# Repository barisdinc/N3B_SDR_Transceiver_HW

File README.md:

# N3B
V/U/SHF and QO-100 SDR Transceiver Project

This project is a SDR receiver transceiver project initiated to have a portable QO-100 Satellite ground station which can receiver on 739 MHz (direct output of a standard TV LNB) and transmit on 2.4 GHz QO-100 uplink frequency.
The basic idea of the SDR is based on Arjante Marvelde's implementation of Guido's uSDX implementation on raspberry pi pico (https://github.com/ArjanteMarvelde/uSDR-pico/).

Instead of HF components as Tyloe detector Analog Devices's IQ modulator and demodulator chips are chosen to be the IQ components.

I will update the documentation as soon as possible.
Baris DINC
OH2UDS / TA7W

initial pictures of qocurrent work done
initial pictures of the working HW 

OH2UDS / TA7W.

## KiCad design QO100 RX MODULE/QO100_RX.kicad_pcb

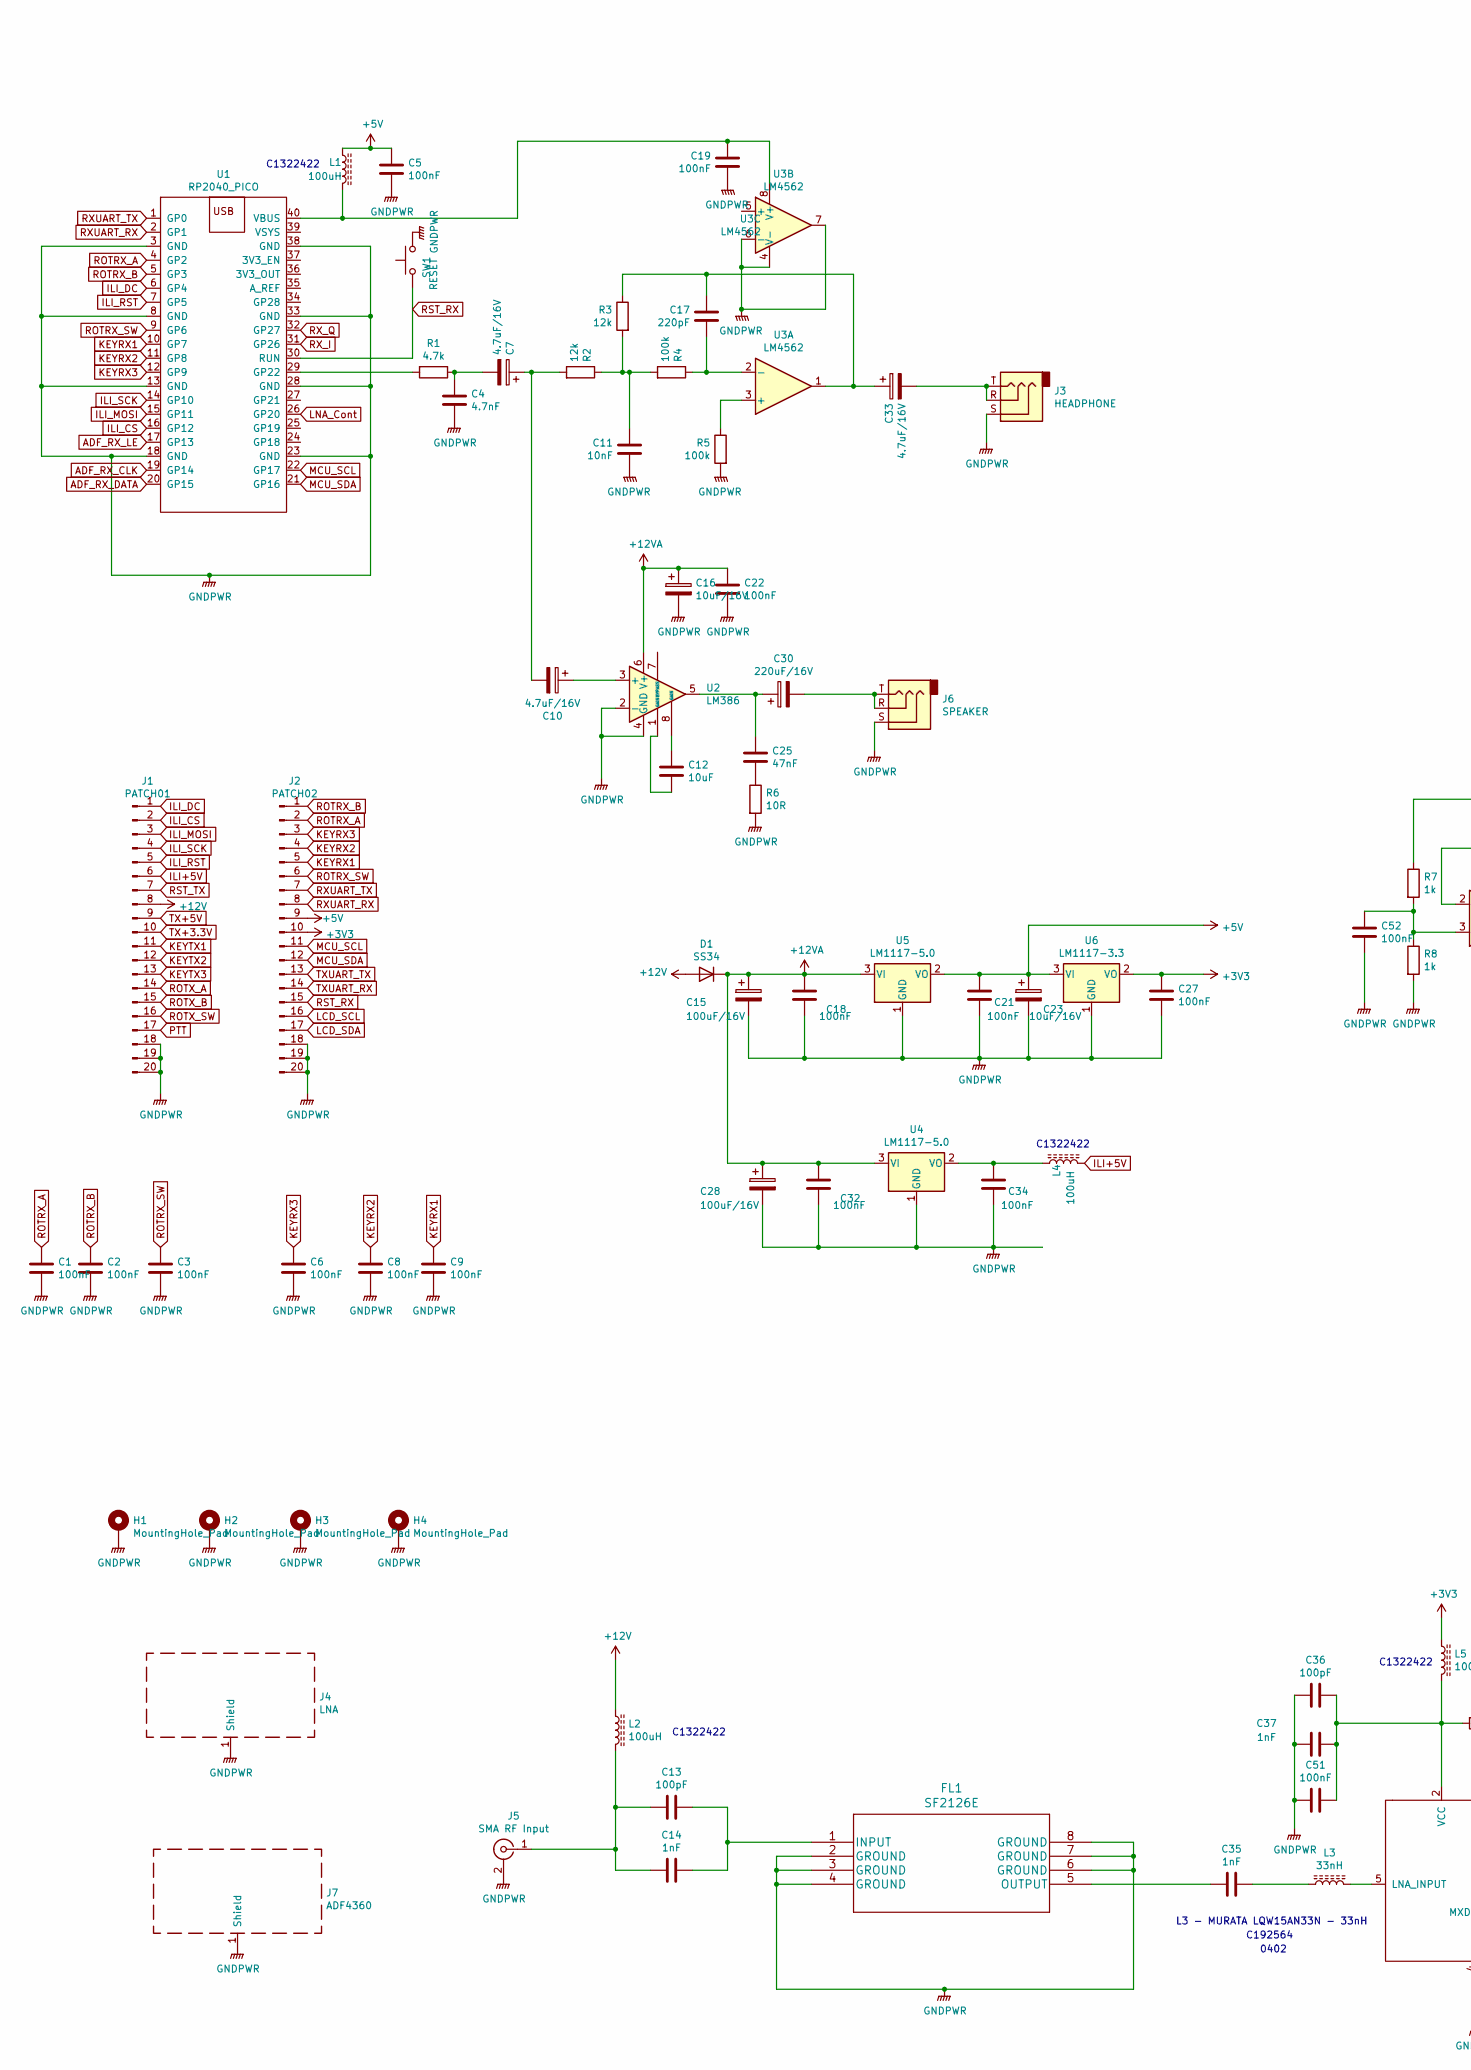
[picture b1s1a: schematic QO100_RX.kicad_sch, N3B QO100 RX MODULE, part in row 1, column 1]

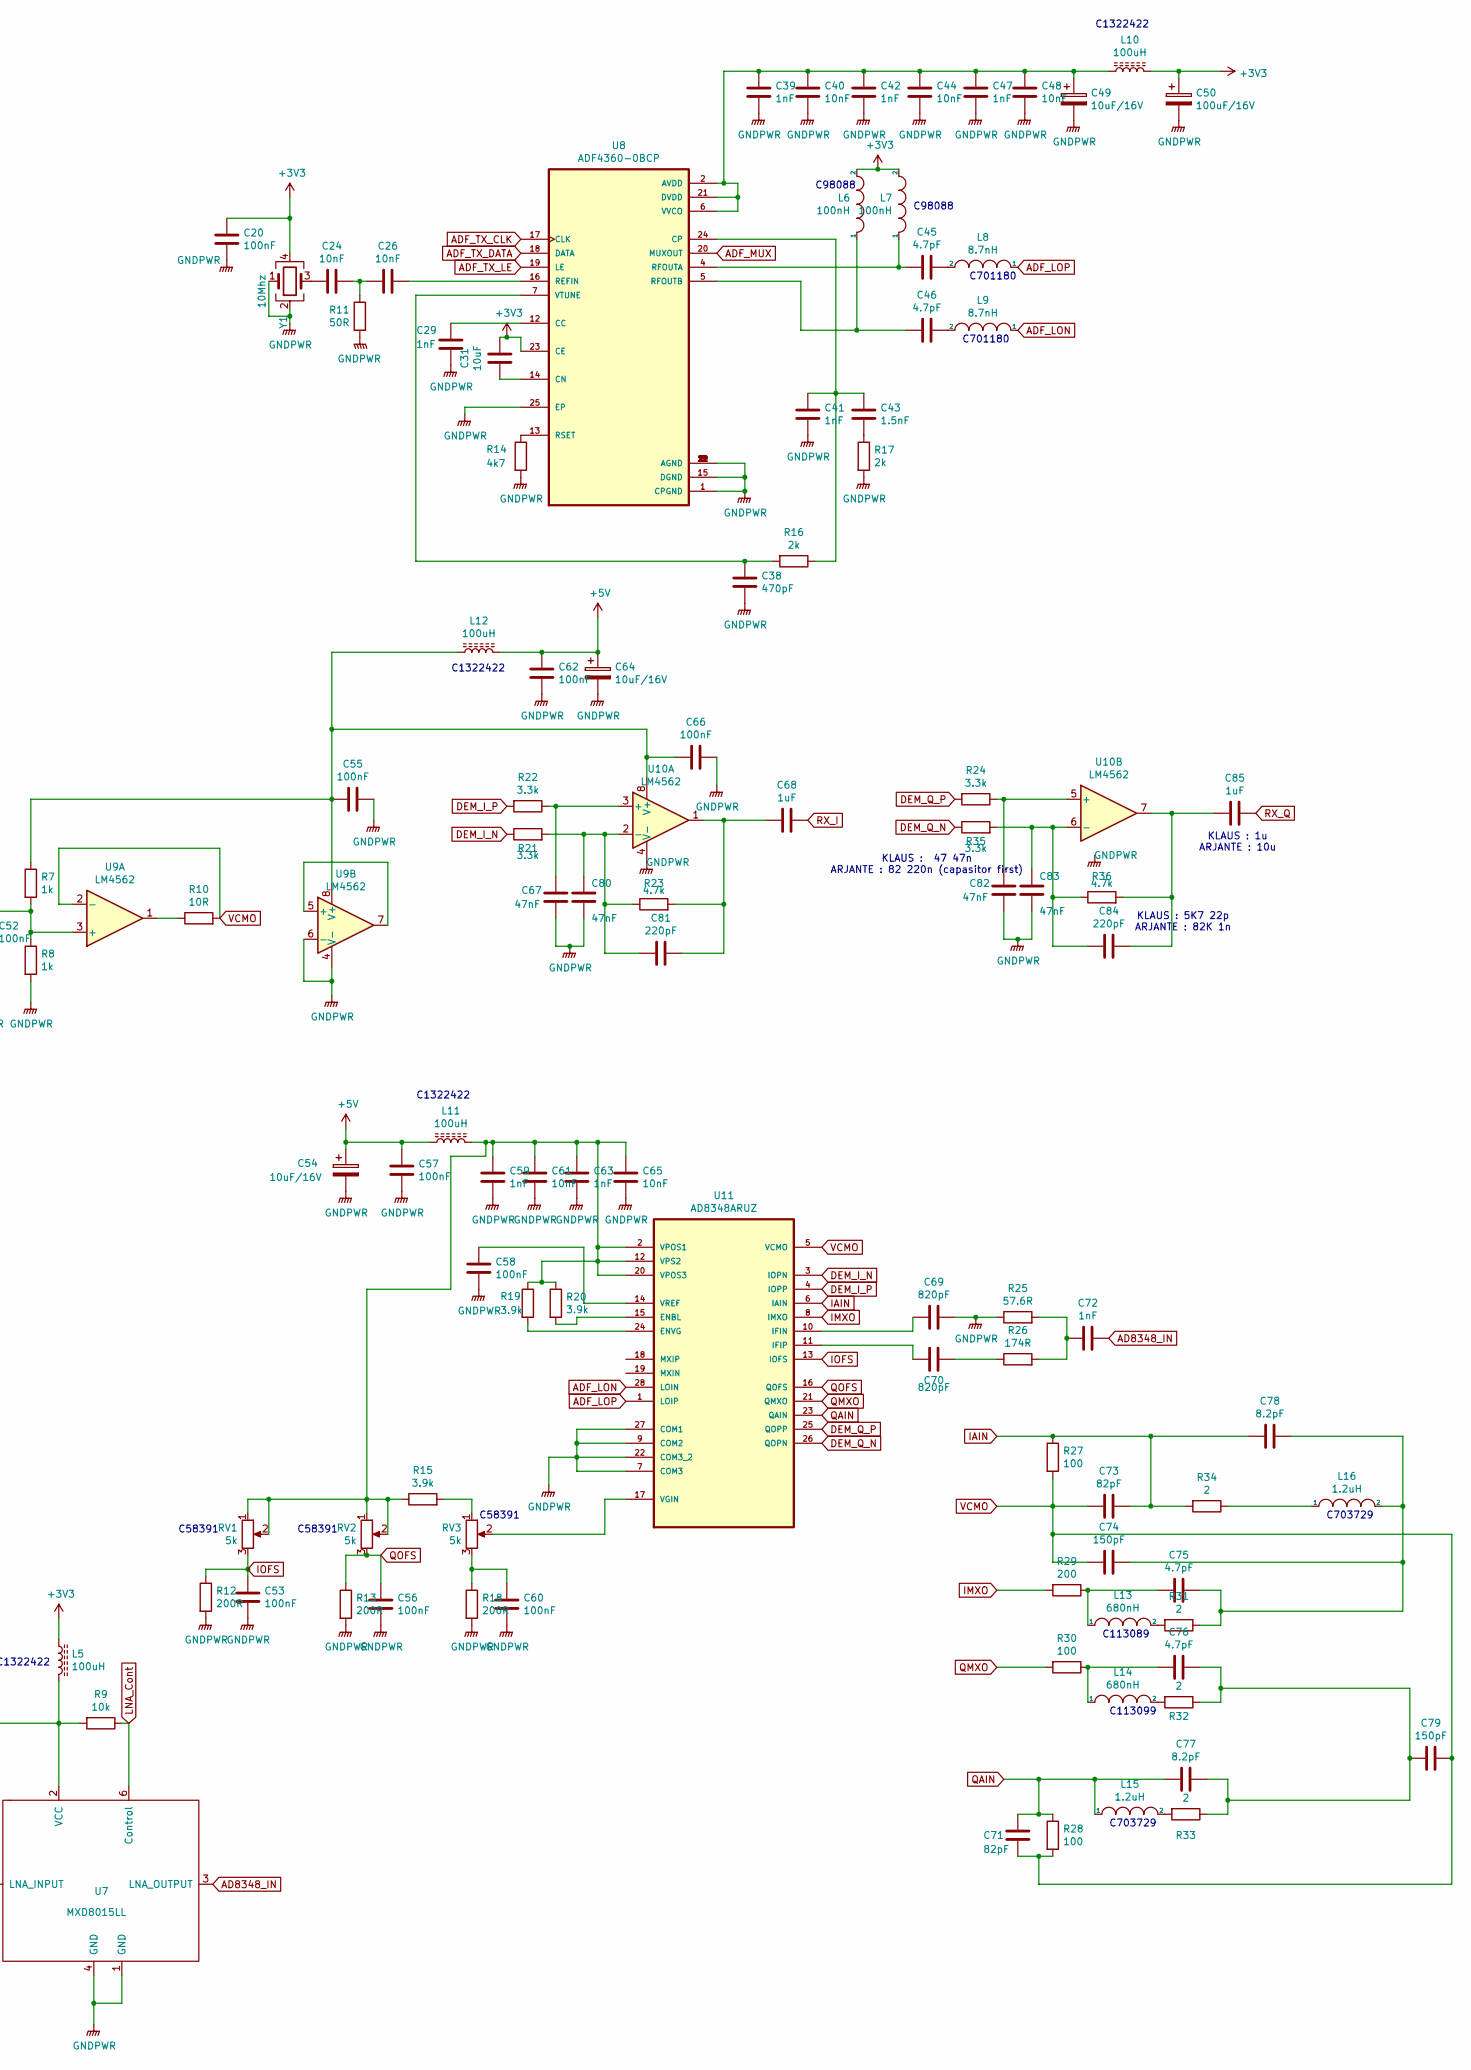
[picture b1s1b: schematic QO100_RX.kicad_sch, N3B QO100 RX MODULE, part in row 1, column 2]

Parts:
C1, C2, C3, C5, C6, C8, C9, C18, C19, C20, C21, C22, C27, C32, C34, C51, C52, C53, C55, C56, C57, C58, C60, C62, C66: 100nF; C_0805_2012Metric
C4: 4.7nF; C_0805_2012Metric
C7, C10, C33: 4.7uF/16V; CP_Elec_4x5.4
C11, C24, C26, C40, C44, C48, C61, C65: 10nF; C_0805_2012Metric
C12, C31: 10uF; C_0805_2012Metric
C13, C36: 100pF; C_0805_2012Metric
C14, C29, C35, C37, C39, C41, C42, C47, C59, C63, C72: 1nF; C_0805_2012Metric
C15, C28, C50: 100uF/16V; CP_Elec_6.3x7.7
C16, C23, C49, C54, C64: 10uF/16V; CP_Elec_4x5.4
C17, C81, C84: 220pF; C_0805_2012Metric
C25, C67, C80, C82, C83: 47nF; C_0805_2012Metric
C30: 220uF/16V; CP_Elec_6.3x7.7
C38: 470pF; C_0805_2012Metric
C43: 1.5nF; C_0805_2012Metric
C45, C46, C75, C76: 4.7pF; C_0805_2012Metric
C68, C85: 1uF; C_0805_2012Metric
C69, C70: 820pF; C_0805_2012Metric
C71, C73: 82pF; C_0805_2012Metric
C74, C79: 150pF; C_0805_2012Metric
C77, C78: 8.2pF; C_0805_2012Metric
D1: SS34; D_SMA
FL1: SF2126E
H1, H2, H3, H4: MountingHole_Pad; MountingHole_3.2mm_M3_DIN965_Pad
J1: PATCH01; PinHeader_1x20_P2.54mm_Vertical
J2: PATCH02; PinHeader_1x20_P2.54mm_Vertical
J3: HEADPHONE; Jack_3.5mm_PJ-320B-SMT_Horizontal_CORR
J4: LNA; Laird_Technologies_BMI-S-102_16.50x16.50mm
J5: SMA RF Input; SMA_Samtec_SMA-J-P-X-ST-EM1_EdgeMount
J6: SPEAKER; Jack_3.5mm_PJ-320B-SMT_Horizontal_CORR
J7: ADF4360; Laird_Technologies_BMI-S-204-F_32.00x32.00mm
L1, L2, L4, L5, L10, L11, L12: 100uH; L_1210_3225Metric
L3: 33nH; L_0402_1005Metric
L6, L7: 100nH; L_0603_1608Metric
L8, L9: 8.7nH; L_0603_1608Metric
L13, L14: 680nH; L_0805_2012Metric
L15, L16: 1.2uH; L_0805_2012Metric
R1, R23, R36: 4.7k; R_0805_2012Metric
R2, R3: 12k; R_0805_2012Metric
R4, R5: 100k; R_0805_2012Metric
R6, R10: 10R; R_0805_2012Metric
R7, R8: 1k; R_0805_2012Metric
R9: 10k; R_0805_2012Metric
R11: 50R; R_0805_2012Metric
R12, R13, R18: 200R; R_0805_2012Metric
R14: 4k7; R_0805_2012Metric
R15, R19, R20: 3.9k; R_0805_2012Metric
R16, R17: 2k; R_0805_2012Metric
R21, R22, R24, R35: 3.3k; R_0805_2012Metric
R25: 57.6R; R_0805_2012Metric
R26: 174R; R_0805_2012Metric
R27, R28, R30: 100; R_0805_2012Metric
R29: 200; R_0805_2012Metric
R31, R32, R33, R34: 2; R_0805_2012Metric
RV1, RV2, RV3: 5k; Potentiometer_Bourns_3314J_Vertical
SW1: RESET; SW_Push_1P1T_NO_6x6mm_H9.5mm
U1: RP2040_PICO; RPI2040_PICO_SMD
U2: LM386; SO-8_3.9x4.9mm_P1.27mm
U3, U9, U10: LM4562; SO-8_3.9x4.9mm_P1.27mm
U4, U5: LM1117-5.0; SOT-223-3_TabPin2
U6: LM1117-3.3; SOT-223-3_TabPin2
U7: MXD8015LL; IC_BGC100GN6E6327XTSA1
U8: ADF4360-0BCP; ADF4360SEDA
U11: AD8348ARUZ; AD8348SEDA; MPN AD8348ARUZ
Y1: 10Mhz; Crystal_SMD_SeikoEpson_FA238V-4Pin_3.2x2.5mm

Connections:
+3V3: C20.1, C27.1, C31.1, C50.1, J2.10, L5.1, L6.2, L7.2, L10.2, U6.2 (VO), U8.23 (CE), Y1.4
+5V: C5.1, C21.1, C23.1, C54.1, C57.1, C62.1, C64.1, J2.9, L1.1, L11.1, L12.2, U5.2 (VO), U6.3 (VI)
+12V: D1.2 (A), J1.8, L2.1
+12VA: C15.1, C16.1, C18.1, C22.1, C28.1, C32.1, D1.1 (K), U2.6 (V+), U4.3 (VI), U5.3 (VI)
AD8348_IN: C72.2, U7.3 (LNA_OUTPUT)
ADF_LON: L9.1, U11.28 (LOIN)
ADF_LOP: L8.1, U11.1 (LOIP)
ADF_MUX: U8.20 (MUXOUT)
ADF_RX_CLK: U1.19 (GP14)
ADF_RX_DATA: U1.20 (GP15)
ADF_RX_LE: U1.17 (GP13)
ADF_TX_CLK: U8.17 (CLK)
ADF_TX_DATA: U8.18 (DATA)
ADF_TX_LE: U8.19 (LE)
DEM_I_N: R21.1, U11.3 (IOPN)
DEM_I_P: R22.2, U11.4 (IOPP)
DEM_Q_N: R35.1, U11.26 (QOPN)
DEM_Q_P: R24.2, U11.25 (QOPP)
GNDPWR: C1.2, C2.2, C3.2, C4.2, C5.2, C6.2, C8.2, C9.2, C11.2, C15.2, C16.2, C18.2, C19.2, C20.2, C21.2, C22.2, C23.2, C27.2, C28.2, C29.2, C32.2, C34.2, C36.2, C37.2, C38.2, C39.2, C40.2, C41.2, C42.2, C44.2, C47.2, C48.2, C49.2, C50.2, C51.2, C52.2, C53.2, C54.2, C55.2, C56.2, C57.2, C58.2, C59.2, C60.2, C61.2, C62.2, C63.2, C64.2, C65.2, C66.1, C67.2, C69.2, C80.2, C82.2, C83.2, FL1.2 (GROUND), FL1.3 (GROUND), FL1.4 (GROUND), FL1.6 (GROUND), FL1.7 (GROUND), FL1.8 (GROUND), H1.1, H2.1, H3.1, H4.1, J1.18, J1.19, J1.20, J2.18, J2.19, J2.20, J3.S, J4.1, J5.2 (Ext), J6.S, J7.1, R5.2, R6.2, R8.2, R11.2, R12.2, R13.2, R14.2, R17.2, R18.2, R25.1, SW1.2, U1.3 (GND), U1.8 (GND), U1.13 (GND), U1.18 (GND), U1.23 (GND), U1.28 (GND), U1.33 (GND), U1.38 (GND), U2.2 (-), U2.4 (GND), U3.4 (V-), U3.6 (-), U3.7, U4.1 (GND), U5.1 (GND), U6.1 (GND), U7.1 (GND), U7.4 (GND), U8.1 (CPGND), U8.3 (AGND), U8.8 (AGND), U8.9 (AGND), U8.10 (AGND), U8.11 (AGND), U8.15 (DGND), U8.22 (AGND), U8.25 (EP), U9.4 (V-), U9.6 (-), U10.4 (V-), U11.7 (COM3), U11.9 (COM2), U11.22 (COM3_2), U11.27 (COM1), Y1.1, Y1.2
IAIN: C73.1, C78.2, R27.1, R34.2, U11.6 (IAIN)
ILI+5V: J1.6, L4.2
ILI_CS: J1.2, U1.16 (GP12)
ILI_DC: J1.1, U1.6 (GP4)
ILI_MOSI: J1.3, U1.15 (GP11)
ILI_RST: J1.5, U1.7 (GP5)
ILI_SCK: J1.4, U1.14 (GP10)
IMXO: R29.2, U11.8 (IMXO)
IOFS: C53.1, R12.1, RV1.3, U11.13 (IOFS)
KEYRX1: C9.1, J2.5, U1.10 (GP7)
KEYRX2: C8.1, J2.4, U1.11 (GP8)
KEYRX3: C6.1, J2.3, U1.12 (GP9)
KEYTX1: J1.11
KEYTX2: J1.12
KEYTX3: J1.13
LCD_SCL: J2.16
LCD_SDA: J2.17
LNA_Cont: R9.1, U1.26 (GP20), U7.6 (Control)
MCU_SCL: J2.11, U1.22 (GP17)
MCU_SDA: J2.12, U1.21 (GP16)
unnamed: C4.1, C7.2, R1.1
unnamed: C10.1, U2.3 (+)
unnamed: C7.1, C10.2, R2.2
unnamed: C11.1, R2.1, R3.2, R4.2
unnamed: C12.1, U2.8 (GAIN)
unnamed: C12.2, U2.1 (GAIN)
unnamed: C13.1, C14.1, FL1.1 (INPUT)
unnamed: C13.2, C14.2, J5.1 (In), L2.2
unnamed: C17.1, C33.1, R3.1, U3.1
unnamed: C17.2, R4.1, U3.2 (-)
unnamed: C19.1, L1.2, U1.40 (VBUS), U3.8 (V+)
unnamed: C24.1, Y1.3
unnamed: C24.2, C26.1, R11.1
unnamed: C25.1, C30.1, U2.5
unnamed: C25.2, R6.1
unnamed: C26.2, U8.16 (REFIN)
unnamed: C29.1, U8.12 (CC)
unnamed: C30.2, J6.R, J6.T
unnamed: C31.2, U8.14 (CN)
unnamed: C33.2, J3.R, J3.T
unnamed: C34.1, L4.1, U4.2 (VO)
unnamed: C35.1, L3.1
unnamed: C35.2, FL1.5 (OUTPUT)
unnamed: C36.1, C37.1, C51.1, L5.2, R9.2, U7.2 (VCC)
unnamed: C38.1, R16.2, U8.7 (VTUNE)
unnamed: C39.1, C40.1, C42.1, C44.1, C47.1, C48.1, C49.1, L10.1, U8.2 (AVDD), U8.6 (VVCO), U8.21 (DVDD)
unnamed: C41.1, C43.1, R16.1, U8.24 (CP)
unnamed: C43.2, R17.1
unnamed: C45.1, L7.1, U8.4 (RFOUTA)
unnamed: C45.2, L8.2
unnamed: C46.1, L6.1, U8.5 (RFOUTB)
unnamed: C46.2, L9.2
unnamed: C52.1, R7.2, R8.1, U9.3 (+)
unnamed: C55.1, C66.2, L12.1, R7.1, U9.8 (V+), U10.8 (V+)
unnamed: C58.1, U11.14 (VREF)
unnamed: C59.1, C61.1, C63.1, C65.1, L11.2, R15.1, R19.1, R20.1, RV1.1, RV1.2, RV2.1, RV2.2, U11.2 (VPOS1), U11.12 (VPS2), U11.20 (VPOS3)
unnamed: C60.1, R18.1, RV3.3
unnamed: C67.1, R22.1, U10.3 (+)
unnamed: C68.2, C81.1, R23.2, U10.1
unnamed: C69.1, U11.10 (IFIN)
unnamed: C70.1, U11.11 (IFIP)
unnamed: C70.2, R26.1
unnamed: C72.1, R25.2, R26.2
unnamed: C74.1, C75.2, C78.1, L16.2, R31.1
unnamed: C75.1, L13.1, R29.1
unnamed: C76.1, L14.1, R30.1
unnamed: C76.2, C77.2, C79.1, R32.1, R33.1
unnamed: C80.1, C81.2, R21.2, R23.1, U10.2 (-)
unnamed: C82.1, R24.1, U10.5 (+)
unnamed: C83.1, C84.2, R35.2, R36.1, U10.6 (-)
unnamed: C84.1, C85.2, R36.2, U10.7
unnamed: L3.2, U7.5 (LNA_INPUT)
unnamed: L13.2, R31.2
unnamed: L14.2, R32.2
unnamed: L15.2, R33.2
unnamed: L16.1, R34.1
unnamed: R1.2, U1.29 (GP22)
unnamed: R5.1, U3.3 (+)
unnamed: R10.1, U9.1
unnamed: R14.1, U8.13 (RSET)
unnamed: R15.2, RV3.1
unnamed: R19.2, U11.24 (ENVG)
unnamed: R20.2, U11.15 (ENBL)
unnamed: RV3.2, U11.17 (VGIN)
unnamed: U9.5 (+), U9.7
PTT: J1.17
QAIN: C71.1, C77.1, L15.1, R28.1, U11.23 (QAIN)
QMXO: R30.2, U11.21 (QMXO)
QOFS: C56.1, R13.1, RV2.3, U11.16 (QOFS)
ROTRX_A: C1.1, J2.2, U1.4 (GP2)
ROTRX_B: C2.1, J2.1, U1.5 (GP3)
ROTRX_SW: C3.1, J2.6, U1.9 (GP6)
ROTX_A: J1.14
ROTX_B: J1.15
ROTX_SW: J1.16
RST_RX: J2.15, SW1.1, U1.30 (RUN)
RST_TX: J1.7
RXUART_RX: J2.8, U1.2 (GP1)
RXUART_TX: J2.7, U1.1 (GP0)
RX_I: C68.1, U1.31 (GP26)
RX_Q: C85.1, U1.32 (GP27)
TX+3.3V: J1.10
TX+5V: J1.9
TXUART_RX: J2.14
TXUART_TX: J2.13
VCMO: C71.2, C73.2, C74.2, C79.2, R10.2, R27.2, R28.2, U9.2 (-), U11.5 (VCMO)

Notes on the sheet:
C1322422
C701180
L3 - MURATA LQW15AN33N - 33nH
C113099
C58391
KLAUS : 1u ARJANTE : 10u
C192564
C98088
C703729
C113089
KLAUS : 5K7 22p ARJANTE : 82K 1n
KLAUS : 47 47n ARJANTE : 82 220n (capasitor first)
0402

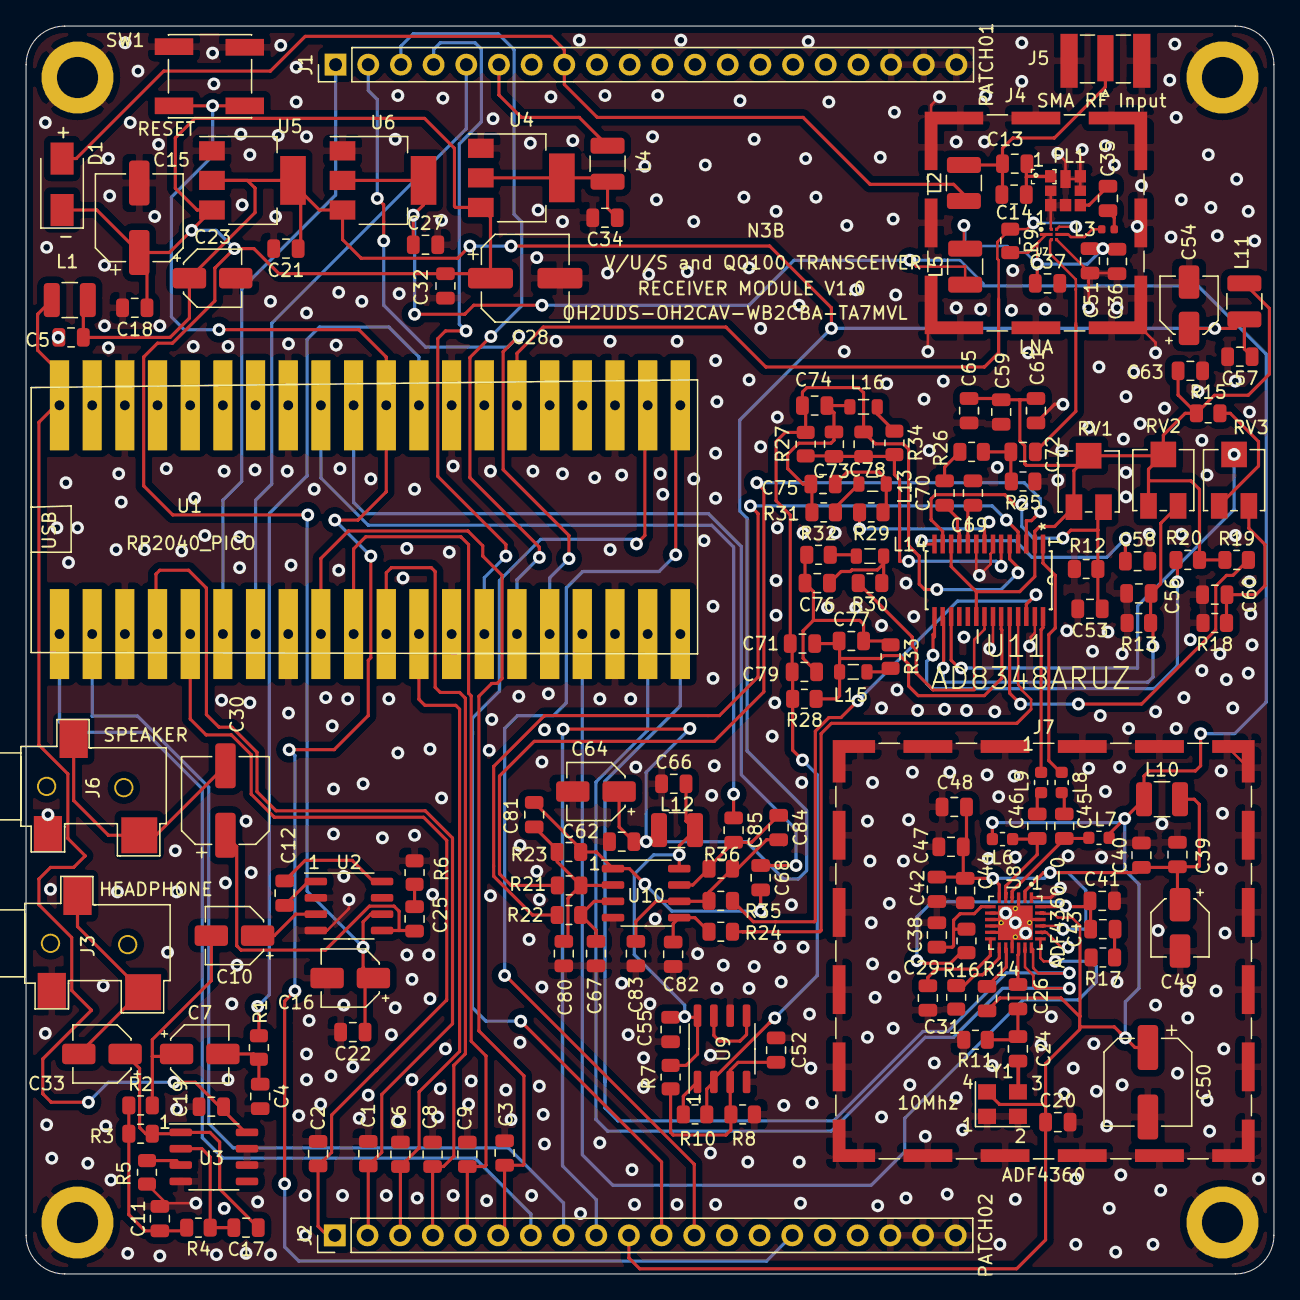
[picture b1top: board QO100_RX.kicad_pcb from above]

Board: 2 copper layers, 97.0 x 97.0 mm, 166 parts (0 on the bottom side), 104 nets.

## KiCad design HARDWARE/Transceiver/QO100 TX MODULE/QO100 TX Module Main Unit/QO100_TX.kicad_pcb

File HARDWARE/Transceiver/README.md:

This folder will contain the transceiver design files

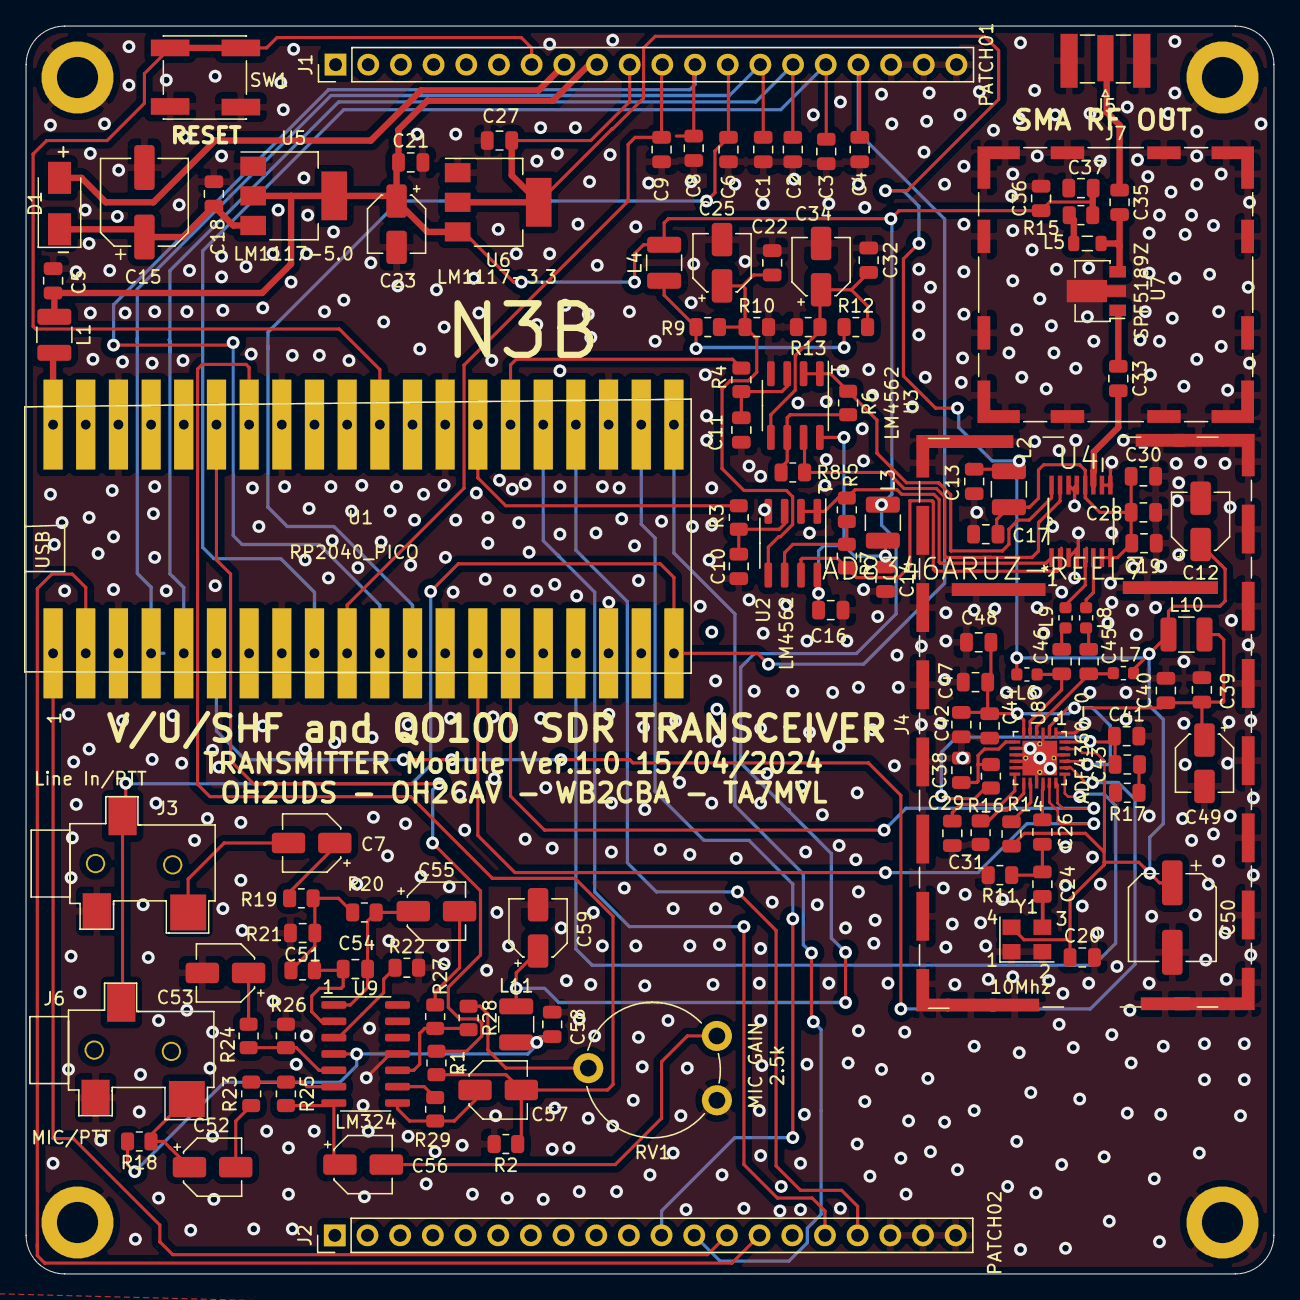
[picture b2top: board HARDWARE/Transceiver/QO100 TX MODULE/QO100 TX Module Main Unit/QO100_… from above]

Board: 2 copper layers, 97.0 x 97.0 mm, 123 parts (0 on the bottom side), 81 nets.

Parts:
C1, C2, C3, C4, C5, C6, C8, C9, C13, C14, C16, C18, C20, C21, C22, C27, C32, C58: 100nF; C_0805_2012Metric
C7, C52, C53, C55, C56, C57: 4.7uF/16V; CP_Elec_4x5.4
C10, C11: 4.7nF; C_0805_2012Metric
C12, C23, C25, C34, C49, C59: 10uF/16V; CP_Elec_4x5.4
C15, C50: 100uF/16V; CP_Elec_6.3x7.7
C17, C24, C26, C30, C40, C44, C48: 10nF; C_0805_2012Metric
C19, C28, C35, C36, C37: 100pF; C_0805_2012Metric
C29, C39, C41, C42, C47: 1nF; C_0805_2012Metric
C31: 10uF; C_0805_2012Metric
C33: 10pF; C_0805_2012Metric
C38: 470pF; C_0805_2012Metric
C43: 1.5nF; C_0805_2012Metric
C45, C46: 4.3pF; C_0805_2012Metric
C51: 2.2nF; C_0805_2012Metric
C54: 120pF; C_0805_2012Metric
D1: SS34; D_SMA
H1, H2, H3, H4: MountingHole_Pad; MountingHole_3.2mm_M3_DIN965_Pad
J1: PATCH01; PinHeader_1x20_P2.54mm_Vertical
J2: PATCH02; PinHeader_1x20_P2.54mm_Vertical
J3: Line In/PTT; Jack_3.5mm_PJ-320B-SMT_Horizontal_CORR
J4: ADF4360+AD8346 SHIELD; Laird_Technologies_BMI-S-210-F_44.00x30.50mm
J5: SMA RF OUT; SMA_Samtec_SMA-J-P-X-ST-EM1_EdgeMount
J6: MIC/PTT; Jack_3.5mm_PJ-320B-SMT_Horizontal_CORR
J7: SP5189 SHIELD; Wuerth_36103205_20x20mm
L1, L2, L3, L4, L10, L11: 100uH; L_1210_3225Metric
L5: 47nH; L_0805_2012Metric
L6, L7: 100nH; L_0603_1608Metric
L8, L9: 8.7nH; L_0603_1608Metric
R1: 51k; R_0805_2012Metric
R2, R3, R4, R5, R6, R8, R23, R24, R27, R28, R29: 10k; R_0805_2012Metric
R7: 1ok; R_0805_2012Metric
R9, R12: 5k6; R_0805_2012Metric
R10, R13: 1k8; R_0805_2012Metric
R11: 50R; R_0805_2012Metric
R14: 4k7; R_0805_2012Metric
R15: 0R; R_0805_2012Metric
R16, R17: 2k; R_0805_2012Metric
R18: 180R; R_0805_2012Metric
R19: 68k; R_0805_2012Metric
R20: 270k; R_0805_2012Metric
R21, R22: 39k; R_0805_2012Metric
R25, R26: 100k; R_0805_2012Metric
RV1: 2.5k; Potentiometer_Piher_PT-10-V10_Vertical
SW1: RESET; SW_Push_1P1T_NO_6x6mm_H9.5mm
U1: RP2040_PICO; RPI2040_PICO_SMD
U2, U3: LM4562; SOIC-8_3.9x4.9mm_P1.27mm
U4: AD8346ARUZ-REEL7; AD8346SEDA
U5: LM1117-5.0; SOT-223-3_TabPin2
U6: LM1117-3.3; SOT-223-3_TabPin2
U7: SPF5189Z; SOT-89-3
U8: ADF4360-0BCP; ADF4360SEDA
U9: LM324; SOIC-14_3.9x8.7mm_P1.27mm
Y1: 10Mhz; Crystal_SMD_SeikoEpson_FA238V-4Pin_3.2x2.5mm

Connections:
+3V3: C12.1, C13.1, C20.1, C27.1, C31.1, C50.1, J1.10, L2.1, L6.2, L7.2, L10.2, U6.2, U8.23, Y1.4
+5V: C5.1, C21.1, C23.1, C36.1, C37.1, C59.1, J1.9, L1.1, L3.2, L4.2, L11.2, R15.1, U5.2, U6.3
+12V: D1.2, J1.8
ADF_LON: L9.1, U4.5
ADF_LOP: L8.1, U4.6
ADF_MUX: U1.6, U8.20
ADF_TX_CLK: U1.14, U8.17
ADF_TX_DATA: U1.15, U8.18
ADF_TX_LE: U1.17, U8.19
GNDPWR: C1.2, C2.2, C3.2, C4.2, C5.2, C6.2, C8.2, C9.2, C10.2, C11.2, C12.2, C13.2, C14.2, C15.2, C16.2, C17.2, C18.2, C19.2, C20.2, C21.2, C22.2, C23.2, C25.2, C27.2, C28.2, C29.2, C30.2, C32.2, C34.2, C36.2, C37.2, C38.2, C39.2, C40.2, C41.2, C42.2, C44.2, C47.2, C48.2, C49.2, C50.2, C51.2, C53.2, C58.2, C59.2, H1.1, H2.1, H3.1, H4.1, J1.18, J1.19, J1.20, J2.18, J2.19, J2.20, J3.S, J4.1, J5.2, J6.S, J7.1, R2.2, R10.2, R11.2, R13.2, R14.2, R17.2, R22.2, R26.2, RV1.3, SW1.2, U1.3, U1.8, U1.13, U1.18, U1.23, U1.28, U1.33, U1.38, U2.4, U3.4, U4.3, U4.4, U4.9, U4.10, U4.13, U4.14, U5.1, U6.1, U7.2, U8.1, U8.3, U8.8, U8.9, U8.10, U8.11, U8.15, U8.22, U8.25, U9.11, Y1.1, Y1.2
IQ_REF1: C22.1, C25.1, R9.2, R10.1, U2.5
IQ_REF2: C32.1, C34.1, R12.2, R13.1, U3.5
I_OUT+: R5.1, U2.1, U2.2, U4.1
I_OUT-: R7.2, U2.7, U4.2
KEY1: C9.1, J1.11, U1.10
KEY2: C8.1, J1.12, U1.11
KEY3: C6.1, J1.13, U1.12
LCD_SCL: J2.16, U1.25
LCD_SDA: J2.17, U1.24
MCU_SCL: J2.11, U1.22
MCU_SDA: J2.12, U1.21
MIC: C57.2, R1.2, R2.1, U1.34
unnamed: C7.1, R19.1
unnamed: C7.2, J3.T
unnamed: C10.1, R3.2, U2.3
unnamed: C11.1, R4.2, U3.3
unnamed: C14.1, C16.1, L3.1, U2.8, U3.8
unnamed: C15.1, C18.1, D1.1, U5.3
unnamed: C17.1, C19.1, C28.1, C30.1, L2.2, U4.7, U4.8, U4.12
unnamed: C24.1, Y1.3
unnamed: C24.2, C26.1, R11.1
unnamed: C26.2, U8.16
unnamed: C29.1, U8.12
unnamed: C31.2, U8.14
unnamed: C33.1, U7.1
unnamed: C33.2, U4.11
unnamed: C35.1, J5.1
unnamed: C35.2, L5.2, U7.3
unnamed: C38.1, R16.2, U8.7
unnamed: C39.1, C40.1, C42.1, C44.1, C47.1, C48.1, C49.1, L10.1, U8.2, U8.6, U8.21
unnamed: C41.1, C43.1, R16.1, U8.24
unnamed: C43.2, R17.1
unnamed: C45.1, L7.1, U8.4
unnamed: C45.2, L8.2
unnamed: C46.1, L6.1, U8.5
unnamed: C46.2, L9.2
unnamed: C51.1, R19.2, R20.2, R21.1
unnamed: C52.1, J6.T, R18.1
unnamed: C52.2, R23.1
unnamed: C53.1, R24.1
unnamed: C54.1, C55.1, R20.1, U9.1
unnamed: C54.2, R21.2, U9.2
unnamed: C55.2, R27.2
unnamed: C56.1, R25.2, U9.7
unnamed: C56.2, RV1.1
unnamed: C57.1, R29.1, U9.8
unnamed: C58.1, L11.1, R18.2, U9.4
unnamed: L1.2, U1.40
unnamed: L4.1, R9.1, R12.1
unnamed: L5.1, R15.2
unnamed: R1.1, U1.35
unnamed: R5.2, R7.1, U2.6
unnamed: R6.2, R8.1, U3.6
unnamed: R14.1, U8.13
unnamed: R22.1, U9.3
unnamed: R23.2, R25.1, U9.6
unnamed: R24.2, R26.1, U9.5
unnamed: R27.1, R28.2, U9.10
unnamed: R28.1, RV1.2
unnamed: R29.2, U9.9
PTT: C4.1, J1.17, J3.R, J6.R, U1.20
Q_OUT+: R6.1, U3.1, U3.2, U4.16
Q_OUT-: R8.2, U3.7, U4.15
RESET: J1.7, SW1.1, U1.30
ROT_A: C1.1, J1.14, U1.4
ROT_B: C2.1, J1.15, U1.5
ROT_SW: C3.1, J1.16, U1.9
TX_I: R3.1, U1.27
TX_Q: R4.1, U1.26
UART_RX: J2.14, U1.2
UART_TX: J2.13, U1.1

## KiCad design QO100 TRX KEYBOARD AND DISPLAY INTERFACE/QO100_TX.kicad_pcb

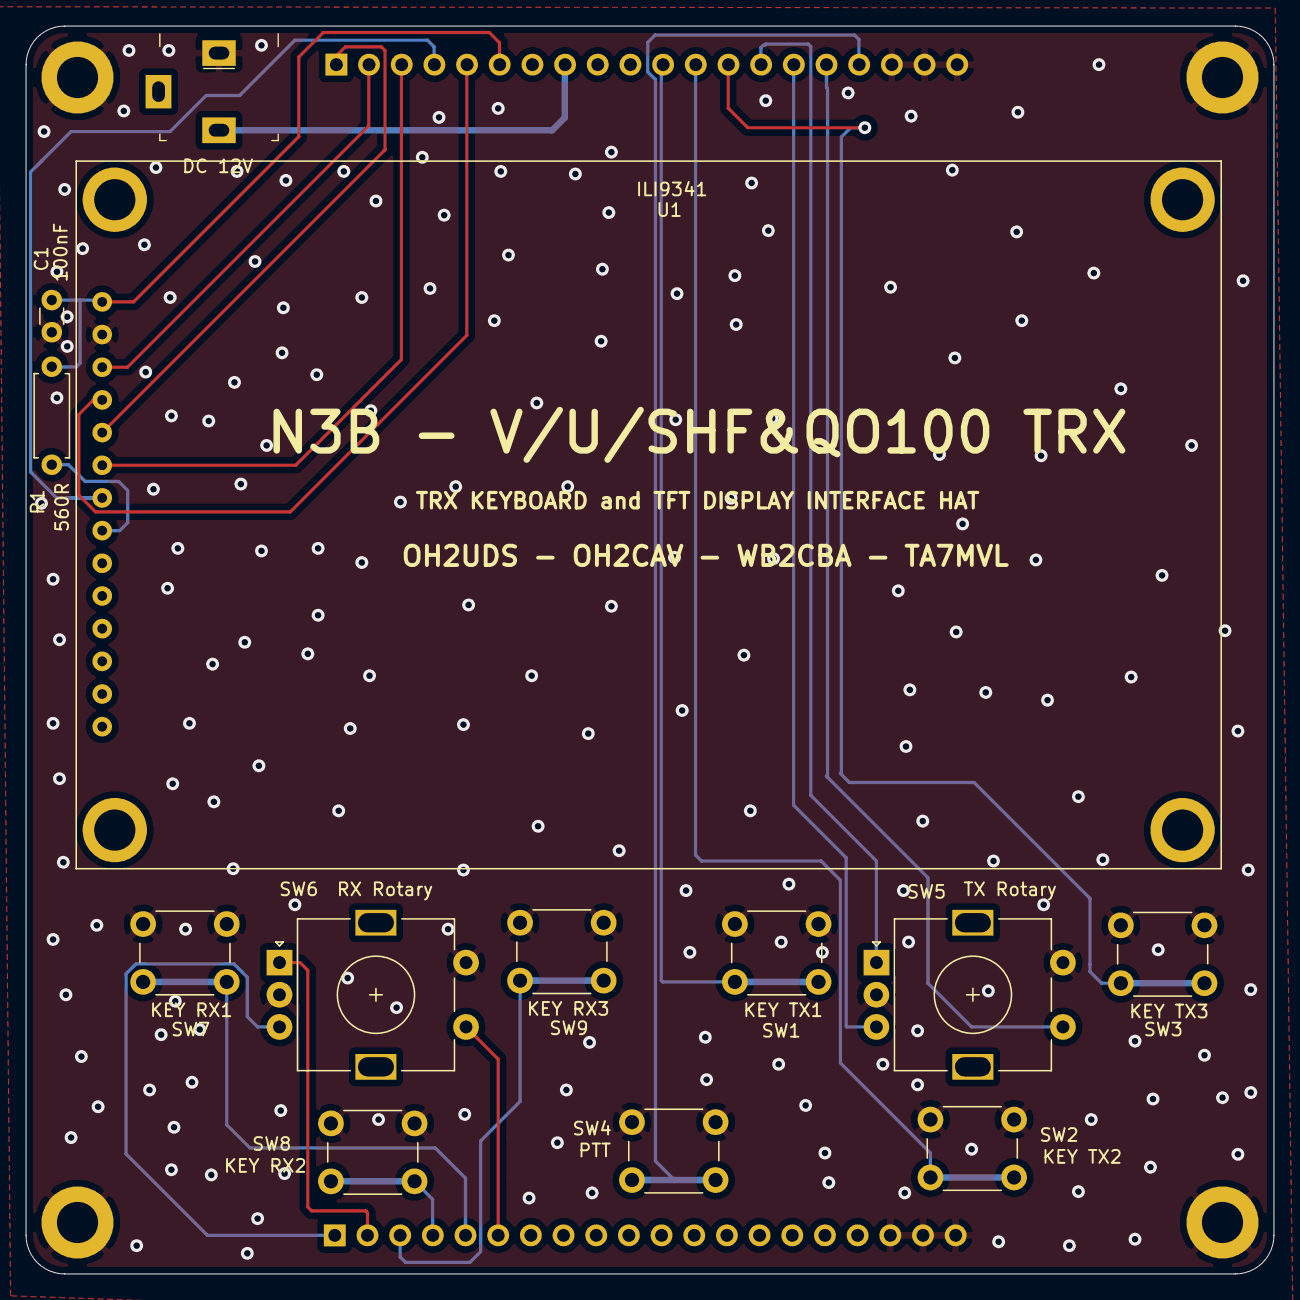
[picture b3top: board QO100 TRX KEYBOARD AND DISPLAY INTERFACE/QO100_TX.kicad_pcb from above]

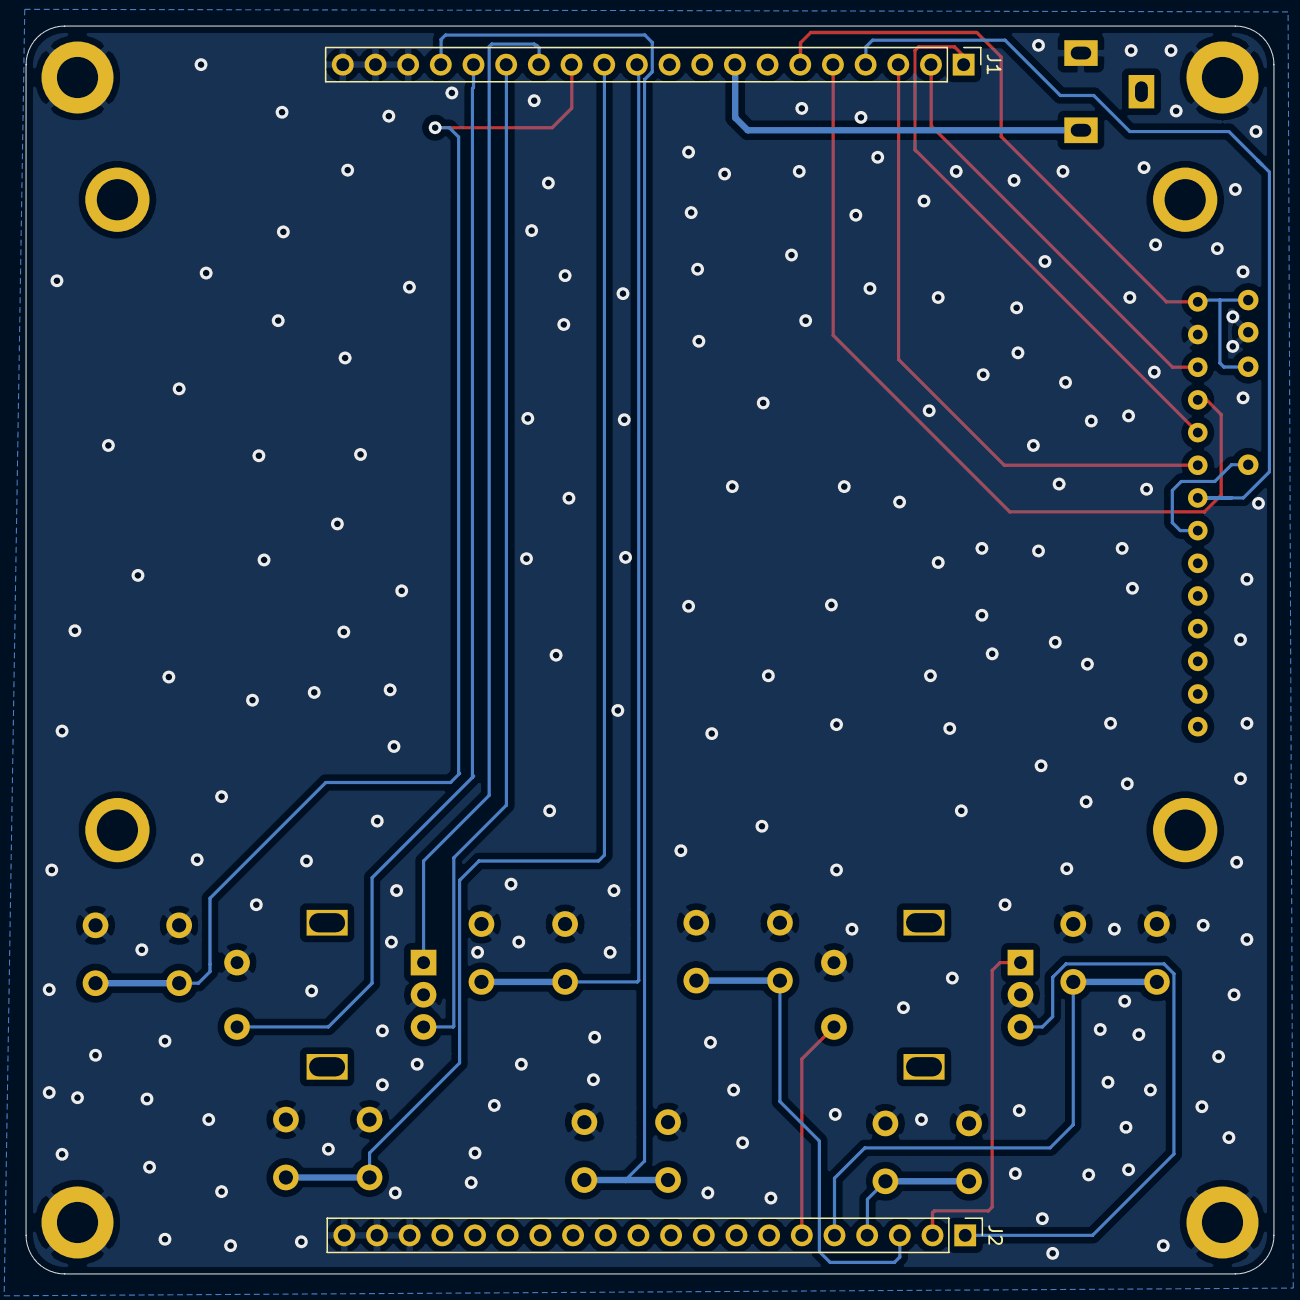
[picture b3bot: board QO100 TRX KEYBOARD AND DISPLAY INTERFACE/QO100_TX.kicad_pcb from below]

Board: 2 copper layers, 97.0 x 97.0 mm, 19 parts (2 on the bottom side), 22 nets.

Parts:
C1: 100nF; C_Disc_D3.0mm_W1.6mm_P2.50mm
H1, H2, H3, H4: MountingHole_Pad; MountingHole_3.2mm_M3_DIN965_Pad
J1: PATCH01; PinHeader_1x20_P2.54mm_Vertical
J2: PATCH02; PinHeader_1x20_P2.54mm_Vertical
J4: PJ-102A; Barrel_Jack_5.5mmODx2.1mmID_PJ-102A
R1: 560R; R_Axial_DIN0207_L6.3mm_D2.5mm_P7.62mm_Horizontal
SW1: KEY TX1; SW_PUSH_6mm
SW2: KEY TX2; SW_PUSH_6mm
SW3: KEY TX3; SW_PUSH_6mm
SW4: PTT; SW_PUSH_6mm
SW5: TX Rotary; RotaryEncoder_Alps_EC11E-Switch_Vertical_H20mm
SW6: RX Rotary; RotaryEncoder_Alps_EC11E-Switch_Vertical_H20mm
SW7: KEY RX1; SW_PUSH_6mm
SW8: KEY RX2; SW_PUSH_6mm
SW9: KEY RX3; SW_PUSH_6mm
U1: ILI9341; ILI9341_32

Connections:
+12V: J1.8, J4.1
GNDPWR: C1.2, H1.1, H2.1, H3.1, H4.1, J1.18, J1.19, J1.20, J2.18, J2.19, J2.20, J4.2, SW1.1, SW2.1, SW3.1, SW4.1, SW5.C, SW5.S2, SW6.C, SW6.S2, SW7.1, SW8.1, SW9.1, U1.2
ILI+5V: C1.1, J1.6, R1.2, U1.1
ILI_CS: J1.2, U1.3
ILI_DC: J1.1, U1.5
ILI_MOSI: J1.3, U1.6
ILI_RST: J1.5, U1.4
ILI_SCK: J1.4, U1.7
KEYRX1: J2.5, SW7.2
KEYRX2: J2.4, SW8.2
KEYRX3: J2.3, SW9.2
KEYTX1: J1.11, SW1.2
KEYTX2: J1.12, SW2.2
KEYTX3: J1.13, SW3.2
unnamed: R1.1, U1.8
PTT: J1.17, SW4.2
ROTRX_A: J2.2, SW6.A
ROTRX_B: J2.1, SW6.B
ROTRX_SW: J2.6, SW6.S1
ROTX_A: J1.14, SW5.A
ROTX_B: J1.15, SW5.B
ROTX_SW: J1.16, SW5.S1

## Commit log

2024-04-16 initial transmitter commits from barb
2024-05-17 folder re-organisations
2024-05-19 Update README.md düzenlendi
2024-06-15 pictures added

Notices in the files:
parts and their libraries:
Copyright 2016 Accelerated Designs. All rights reserved.
